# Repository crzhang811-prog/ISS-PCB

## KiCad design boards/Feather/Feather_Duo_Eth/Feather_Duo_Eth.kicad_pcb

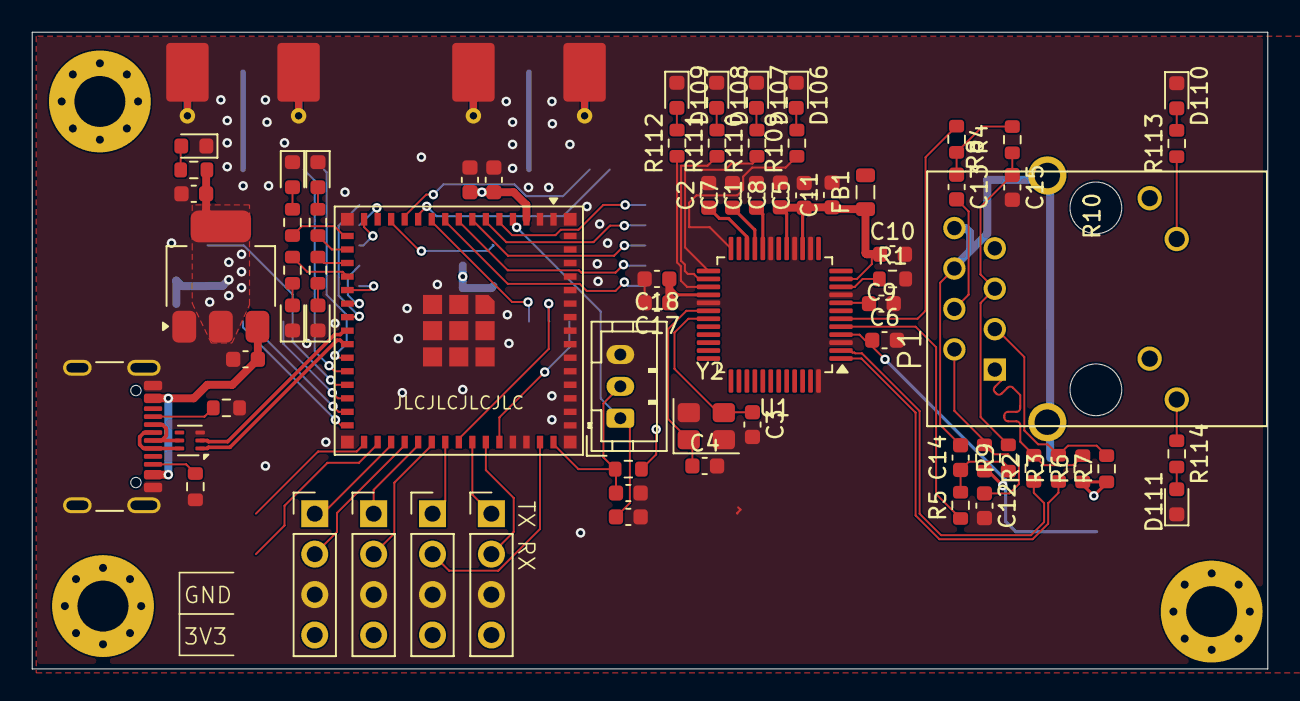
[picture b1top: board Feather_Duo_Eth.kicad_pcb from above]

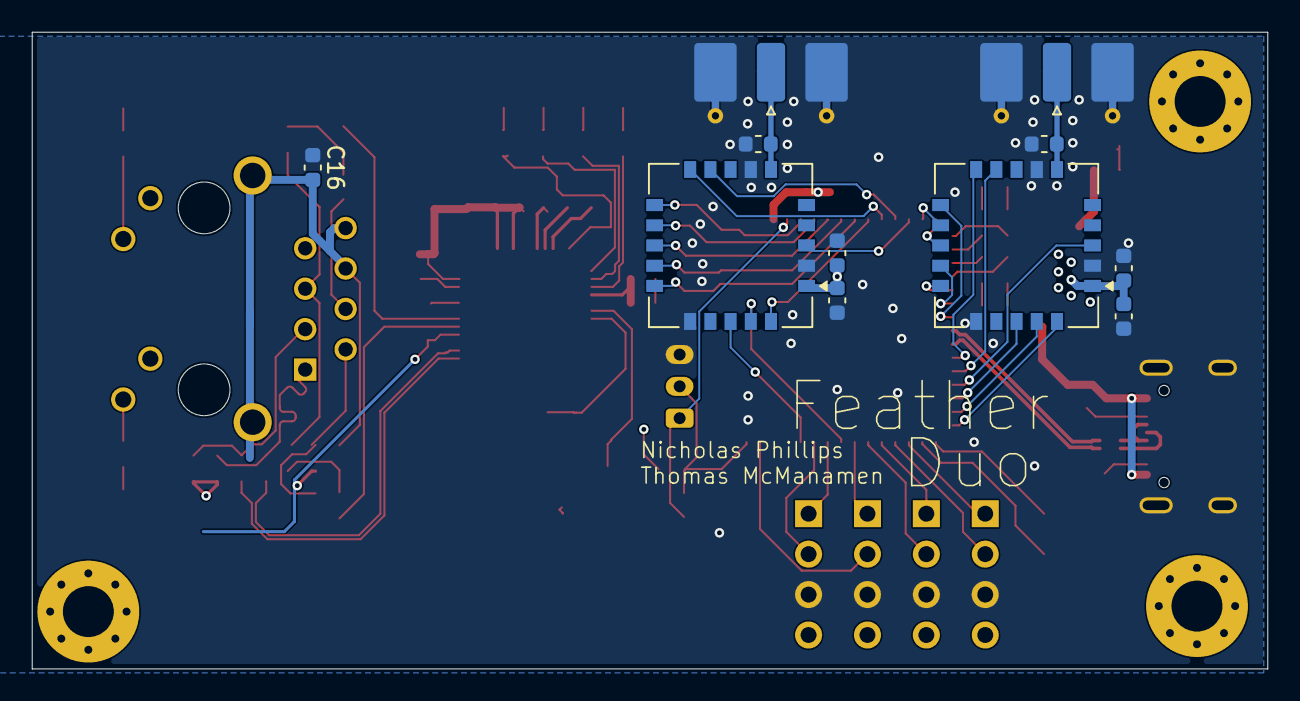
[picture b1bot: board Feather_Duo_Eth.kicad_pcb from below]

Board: 4 copper layers, 77.6 x 40.0 mm, 85 parts (11 on the bottom side), 85 nets.

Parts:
C1: 4.7uF; C_0603_1608Metric
C2, C15, C202, C302: 10nF; C_0603_1608Metric
C3, C4: 27pF; C_0603_1608Metric
C5, C6, C7, C8, C9, C10, C17, C102: 0.1uF; C_0603_1608Metric
C11, C18, C105, C201, C301: 10uF; C_0603_1608Metric
C12: 22nF; C_0603_1608Metric
C13, C14: 6.8nF; C_0603_1608Metric
C16: 1nF; C_0603_1608Metric
C101, C106: 22uF; C_0603_1608Metric
C103, C104: 1uF; C_0603_1608Metric
D101, D105, D106: RED LED; LED_0603_1608Metric
D102, D107: ORANGE LED; LED_0603_1608Metric
D103, D108, D111: GREEN LED; LED_0603_1608Metric
D104, D109: BLUE LED; LED_0603_1608Metric
D110: YELLOW LED; LED_0603_1608Metric
FB1: FerriteBead_Small; L_0805_2012Metric
H101, H102, H103: M3; MountingHole_3.2mm_M3_Pad_Via
J102, J104, J105, J107: Conn_01x04; PinHeader_1x04_P2.54mm_Vertical
J103: Conn_01x03; JST_PH_B3B-PH-K_1x03_P2.00mm_Vertical
J106: USB4105-GF-A; USB_C_Receptacle_GCT_USB4105-xx-A_16P_TopMnt_Horizontal
J201, J301: SMA; SMA_Molex_73251-2120_EdgeMount_Horizontal
L201, L301: 330nH; L_0603_1608Metric
P1: J1B1211CCD
R1: 12.4k; R_0603_1608Metric
R2, R3, R4, R5: 33; R_0603_1608Metric
R6, R7, R9, R10: 49.9; R_0603_1608Metric
R8: 10; R_0603_1608Metric
R101: 20k; R_0603_1608Metric
R102, R103, R104, R105, R108, R109, R110, R111, R112, R113, R114: 1k; R_0603_1608Metric
R106, R107: 5.1k; R_0603_1608Metric
U1: W5500; LQFP-48_7x7mm_P0.5mm
U101: ESP32-S3-MINI-1U; ESP32-S2-MINI-1U
U102: ECMF02-2AMX6; ST_UQFN-6L_1.5x1.7mm_P0.5mm
U103: AMS1117-3.3; SOT-223-3_TabPin2
U201, U301: E22-400MM22S
Y2: Crystal_GND24; Crystal_SMD_3225-4Pin_3.2x2.5mm

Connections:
+3V3: C17.1, C18.1, C101.2, C102.2, C106.1, C201.1, C202.1, C301.1, C302.1, FB1.2, J102.4, J104.4, J105.4, J107.4, P1.10 (GRN+), P1.12 (YLW+), R101.1, R108.1, U1.28 (VDD), U101.3 (3V3), U103.2 (VO), U201.1 (VCC), U301.1 (VCC)
+3V3A: C5.1, C6.1, C7.1, C8.1, C9.1, C10.1, C11.1, FB1.1, R6.1, R7.1, R8.1, U1.4 (AVDD), U1.8 (AVDD), U1.11 (AVDD), U1.15 (AVDD), U1.17 (AVDD), U1.21 (AVDD)
+5V: C105.1, J106.A4 (VBUS), J106.A9 (VBUS), J106.B4 (VBUS), J106.B9 (VBUS), U103.3 (VI)
/ACTLED: R112.1, U1.27 (ACTLED)
/ACT_LED: P1.11 (YLW-), R113.1
/BOOT: C104.1, J103.1, U101.4 (IO0)
/D+: J106.A6 (D+), J106.B6 (D+), U102.6 (D+_out)
/D-: J106.A7 (D-), J106.B7 (D-), U102.5 (D-_out)
/DUPLED: R111.1, U1.26 (DUPLED)
/E22_BUSY_0: U101.5 (IO1), U201.11 (BUSY)
/E22_BUSY_1: U101.22 (IO18), U301.11 (BUSY)
/E22_CS_0: U101.8 (IO4), U201.14 (NSS), U301.14 (NSS)
/E22_DI01_0: U101.10 (IO6), U201.20 (DIO1)
/E22_DI01_1: U101.30 (IO48), U301.20 (DIO1)
/E22_DI02_0: U101.38 (IO42), U201.19 (DIO2)
/E22_DI02_1: U101.29 (IO34), U301.19 (DIO2)
/E22_DI03_0: U101.41 (IO45), U201.18 (DIO3)
/E22_DI03_1: U101.28 (IO33), U301.18 (DIO3)
/E22_RESET_0: U101.13 (IO9), U201.3 (NRST)
/E22_RESET_1: U101.27 (IO47), U301.3 (NRST)
/E22_RXEN_0: U101.11 (IO7), U201.10 (RXEN)
/E22_RXEN_1: U101.25 (IO21), U301.10 (RXEN)
/E22_TXEN_0: U101.12 (IO8), U201.9 (TXEN)
/E22_TXEN_1: U101.26 (IO26), U301.9 (TXEN)
/IO37: J102.1, U101.33 (IO37)
/IO38: J102.2, U101.34 (IO38)
/IO39: J104.1, U101.35 (IO39)
/IO40: J104.2, U101.36 (IO40)
/IO41: J105.1, U101.37 (IO41)
/IO46: J105.2, U101.44 (IO46)
/LED_BLUE: R105.1, U101.16 (IO12)
/LED_GREEN: R104.1, U101.17 (IO13)
/LED_ORANGE: R103.1, U101.18 (IO14)
/LED_RED: R102.1, U101.19 (IO15)
/LINKLED: R110.1, U1.25 (LINKLED)
/LINK_LED: P1.9 (GRN-), R114.1
/RESET: C103.1, J103.2, R101.2, U101.45 (EN)
/RX: J107.2, U101.40 (RXD0)
/RXN: R5.1, U1.5 (RXN)
/RXP: R4.1, U1.6 (RXP)
/SPDLED: R109.1, U1.24 (SPDLED)
/SPI_MISO_0: U101.6 (IO2), U201.12 (MISO), U301.12 (MISO)
/SPI_MISO_1: U1.34 (MISO), U101.14 (IO10)
/SPI_MOSI_0: U101.7 (IO3), U201.13 (MOSI), U301.13 (MOSI)
/SPI_MOSI_1: U1.35 (MOSI), U101.15 (IO11)
/SPI_SCK_0: U101.9 (IO5), U201.15 (SCK), U301.15 (SCK)
/SPI_SCK_1: U1.33 (SCLK), U101.20 (IO16)
/TX: J107.1, U101.39 (TXD0)
/TXN: R3.1, U1.1 (TXN)
/TXP: R2.1, U1.2 (TXP)
/USB_D+: U101.24 (IO20), U102.1 (D+_in)
/USB_D-: U101.23 (IO19), U102.2 (D-_in)
/W5500_CS_0: U1.32 (~SCS), U101.21 (IO17)
/W5500_INT: U1.36 (~INT), U101.32 (IO36)
/W5500_RESET: U1.37 (~RST), U101.31 (IO35)
CHASSIS_GND: C16.2, P1.8 (GH_GND@1), P1.13 (CH_GND@2), P1.14 (CH_GND@3)
GND: C1.2, C2.2, C3.2, C4.2, C5.2, C6.2, C7.2, C8.2, C9.2, C10.2, C11.2, C12.2, C15.2, C16.1, C17.2, C18.2, C101.1, C102.1, C103.2, C104.2, C105.2, C106.2, C201.2, C202.2, C301.2, C302.2, D101.1 (K), D102.1 (K), D103.1 (K), D104.1 (K), D105.1 (K), D106.1 (K), D107.1 (K), D108.1 (K), D109.1 (K), D110.1 (K), D111.1 (K), J102.3, J103.3, J104.3, J105.3, J106.A1 (GND), J106.A12 (GND), J106.B1 (GND), J106.B12 (GND), J106.S1 (SHIELD), J107.3, J201.2 (Ext), J301.2 (Ext), L201.2, L301.2, R1.2, R106.2, R107.2, U1.3 (AGND), U1.9 (AGND), U1.14 (AGND), U1.16 (AGND), U1.19 (AGND), U1.29 (GND), U1.48 (AGND), U101.1 (GND), U101.2 (GND), U101.42 (GND), U101.43 (GND), U101.46 (GND), U101.47 (GND), U101.48 (GND), U101.49 (GND), U101.50 (GND), U101.51 (GND), U101.52 (GND), U101.53 (GND), U101.54 (GND), U101.55 (GND), U101.56 (GND), U101.57 (GND), U101.58 (GND), U101.59 (GND), U101.60 (GND), U101.61 (GND), U101.62 (GND), U101.63 (GND), U101.64 (GND), U101.65 (GND), U102.3 (GND), U103.1 (GND), U201.2 (GND), U201.7 (GND), U201.16 (GND), U301.2 (GND), U301.7 (GND), U301.16 (GND), Y2.2 (G), Y2.4 (G)
unnamed: C13.1, R4.2, R10.1
unnamed: C14.1, R5.2, R9.1
unnamed: D101.2 (A), R102.2
unnamed: D102.2 (A), R103.2
unnamed: D103.2 (A), R104.2
unnamed: D104.2 (A), R105.2
unnamed: D105.2 (A), R108.2
unnamed: D106.2 (A), R109.2
unnamed: D107.2 (A), R110.2
unnamed: D108.2 (A), R111.2
unnamed: D109.2 (A), R112.2
unnamed: D110.2 (A), R113.2
unnamed: D111.2 (A), R114.2
unnamed: J106.A5 (CC1), R106.1
unnamed: J106.B5 (CC2), R107.1
unnamed: J201.1 (In), L201.1, U201.6 (ANT)
unnamed: J301.1 (In), L301.1, U301.6 (ANT)
unnamed: C15.1, P1.5 (RCT), R9.2, R10.2
unnamed: C13.2, P1.4 (RD+)
unnamed: C14.2, P1.6 (RD-)
unnamed: C12.1, P1.2 (TCT), R8.2
unnamed: P1.1 (TD+), R2.2, R6.2
unnamed: P1.3 (TD-), R3.2, R7.2
unnamed: C2.1, U1.22 (1V2O)
unnamed: R1.1, U1.10 (EXRES1)
unnamed: C1.1, U1.20 (TOCAP)
unnamed: C4.1, U1.30 (XI/CLKIN), Y2.1
unnamed: C3.1, U1.31 (XO), Y2.3
